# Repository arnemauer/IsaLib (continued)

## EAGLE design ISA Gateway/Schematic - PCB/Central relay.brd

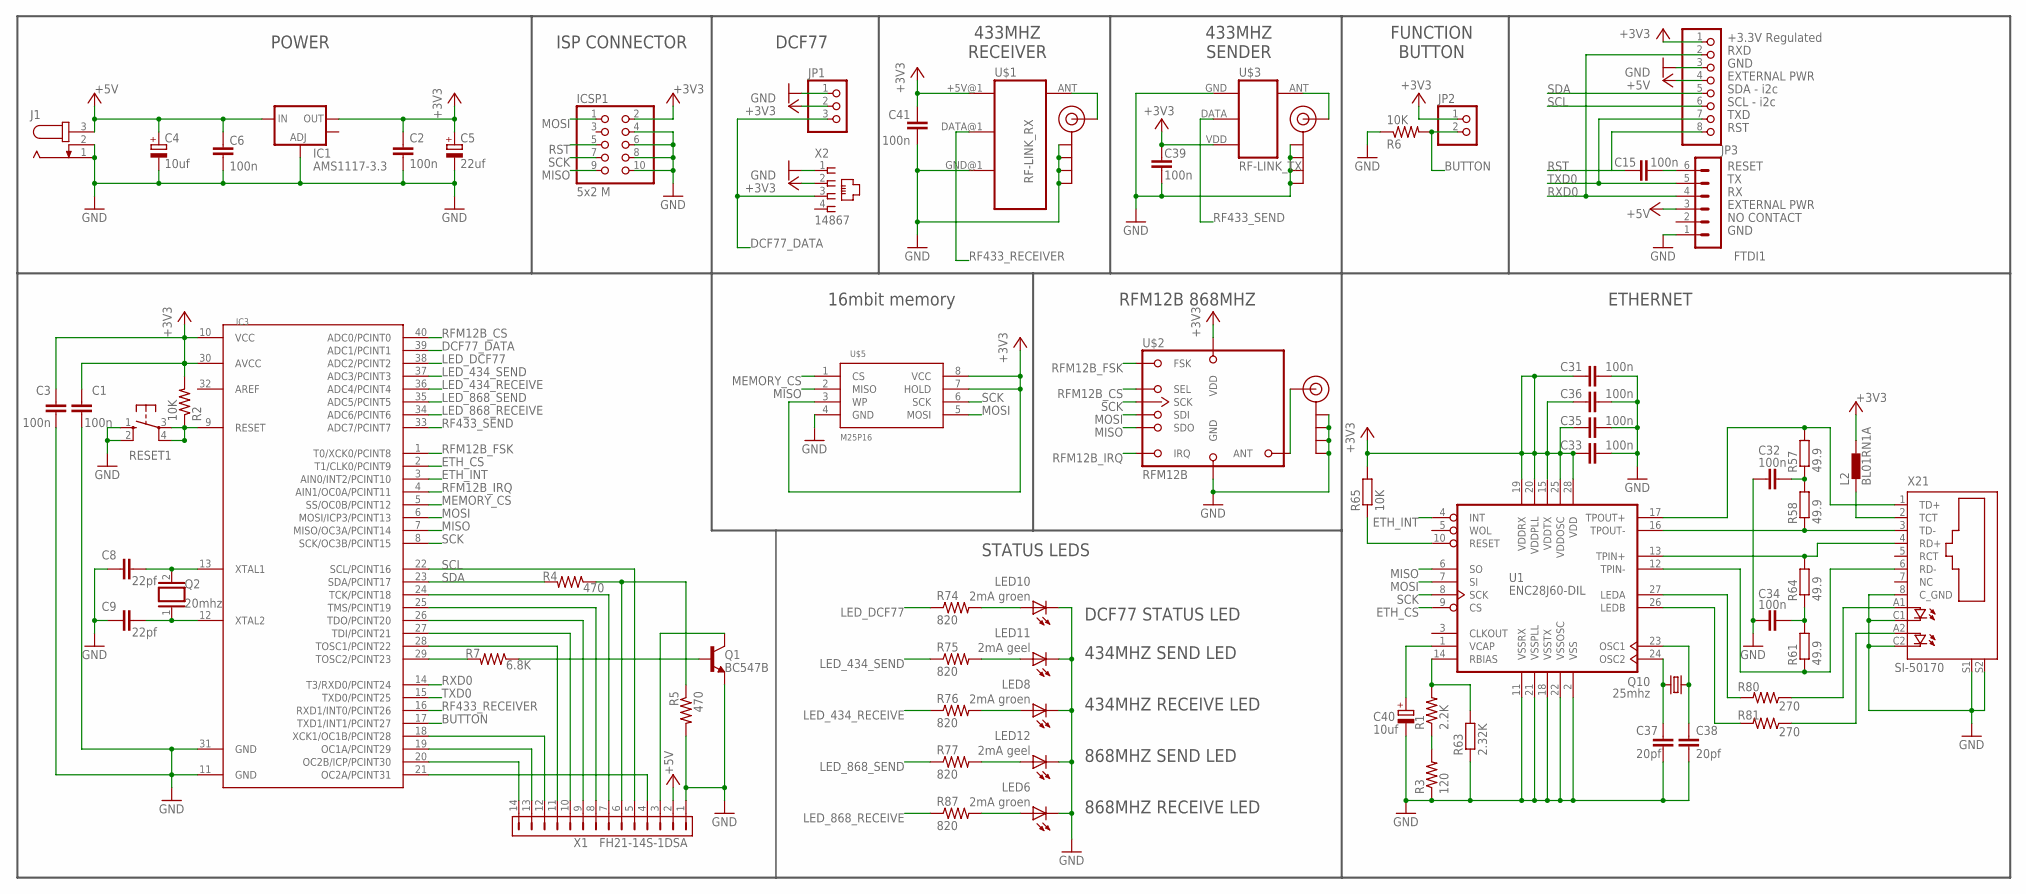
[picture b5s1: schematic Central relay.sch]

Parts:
C1, C2, C3, C6, C31, C32, C33, C34, C35, C36, C39, C41: 100n; 0805
C4, C40: 10uf; E2,5-6E
C5: 22uf; E2,5-6E
C8, C9: 22pf; 0805
C15: 100n; C025-025X050
C37, C38: 20pf; 0805
FTDI1: FTDI; MA06-1
IC1: AMS1117-3.3; SOT223
IC3: MEGA1284P; DIL40
ICSP1: 5x2 M; 2X05
J1: JACK-PLUG0; SPC4077
J$1, J$2, J$3: SMA_EDGE; SMA-EDGE
JP1: PINHD-1X3; 1X03
JP2: PINHD-1X2; 1X02
JP3: PINHD-1X8; 1X08
L2: BL01RN1A
LED6, LED8, LED10: 2mA groen; LED5MM
LED11, LED12: 2mA geel; LED5MM
Q1: BC547B; TO92
Q2: 20mhz; QS
Q10: 25mhz; HC49/S
R1: 2.2K; 0805
R2, R6: 10K; 0805
R3: 120; 0805
R4, R5: 470; 0805
R7: 6.8K; 0805
R57, R58, R61, R64: 49.9; 0207/7
R63: 2.32K; 0207/7
R65: 10K; 0207/7
R74, R75, R76, R77, R87: 820; 0805
R80, R81: 270; 0805
RESET1: 10-XX; B3F-10XX
U1: ENC28J60-DIL; DIL28-3
U$1: RF-LINK_RX
U$2: RFM12B; RFM12B-BREAKOUT-BASE
U$3: RF-LINK_TX
U$5: M25P16; SO08
X1: FH21-14S-1DSA
X2: 14867
X21: SI-50170

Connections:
+3V3: C1.2, C2.2, C3.2, C5.+, C31.1, C33.1, C35.2, C36.2, C39.2, C41.1, IC1.2 (OUT), IC3.10 (VCC), IC3.30 (AVCC), ICSP1.2, JP1.2, JP2.1, JP3.1, L2.2, R2.2, R65.2, U1.15 (VDDTX), U1.19 (VDDRX), U1.20 (VDDPLL), U1.25 (VDDOSC), U1.28 (VDD), U$1.+5V@1 (+5V), U$2.9 (VDD), U$3.VDD (GND), U$5.3 (WP), U$5.7 (HOLD), U$5.8 (VCC), X2.2
+5V: C4.+, C6.2, FTDI1.3, IC1.3 (IN), J1.3, JP3.4, X1.2
BUTTON: IC3.17 (TXD1/INT1/PCINT27), JP2.2, R6.2
DCF77_DATA: IC3.39 (ADC1/PCINT1), JP1.3, X2.3
ETH_CS: IC3.2 (T1/CLK0/PCINT9), U1.9 (CS)
ETH_INT: IC3.3 (AIN0/INT2/PCINT10), U1.4 (INT)
GND: C1.1, C2.1, C3.1, C4.-, C5.-, C6.1, C8.2, C9.2, C31.2, C32.1, C33.2, C34.1, C35.1, C36.1, C37.1, C38.1, C39.1, C40.-, C41.2, FTDI1.1, IC1.1 (ADJ), IC3.11 (GND), IC3.31 (GND), ICSP1.4, ICSP1.6, ICSP1.8, ICSP1.10, J1.1, J1.2, J$1.GND@0 (GND), J$1.GND@1 (GND), J$1.GND@2 (GND), J$1.GND@3 (GND), J$2.GND@0 (GND), J$2.GND@1 (GND), J$2.GND@2 (GND), J$2.GND@3 (GND), J$3.GND@0 (GND), J$3.GND@1 (GND), J$3.GND@2 (GND), J$3.GND@3 (GND), JP1.1, JP3.3, LED6.K (C), LED8.K (C), LED10.K (C), LED11.K (C), LED12.K (C), Q1.1 (E), R3.1, R5.2, R6.1, R63.1, RESET1.1 (S), RESET1.2 (S1), U1.2 (VSS), U1.11 (VSSRX), U1.18 (VSSTX), U1.21 (VSSPLL), U1.22 (VSSOSC), U$1.GND@1 (GND), U$2.10 (GND), U$3.GND (+5V), U$5.4 (GND), X1.1, X2.1, X21.8 (C_GND), X21.C1 (C), X21.C2 (C1), X21.S1, X21.S2
LED_434_RECEIVE: IC3.36 (ADC4/PCINT4), R76.1
LED_434_SEND: IC3.37 (ADC3/PCINT3), R75.1
LED_868_RECEIVE: IC3.34 (ADC6/PCINT6), R87.1
LED_868_SEND: IC3.35 (ADC5/PCINT5), R77.1
LED_DCF77: IC3.38 (ADC2/PCINT2), R74.1
MEMORY_CS: IC3.5 (SS/OC0B/PCINT12), U$5.1 (CS)
MISO: IC3.7 (MISO/OC3A/PCINT14), ICSP1.9, U1.6 (SO), U$2.1 (SDO), U$5.2 (MISO)
MOSI: IC3.6 (MOSI/ICP3/PCINT13), ICSP1.1, U1.7 (SI), U$2.12 (SDI), U$5.5 (MOSI)
unnamed: J$2.SIG (SIGNAL), U$1.ANT
unnamed: R80.1, X21.A1 (A)
unnamed: J$3.SIG (SIGNAL), U$3.ANT
unnamed: R1.1, R3.2
unnamed: R1.2, R63.2, U1.14 (RBIAS)
unnamed: R81.1, X21.A2 (A1)
unnamed: LED8.A, R76.2
unnamed: IC3.21 (OC2A/PCINT31), X1.4
unnamed: Q1.3 (C), X1.3
unnamed: Q1.2 (B), R7.1
unnamed: R4.1, R5.1, X1.6
unnamed: IC3.29 (TOSC2/PCINT23), R7.2
unnamed: LED11.A, R75.2
unnamed: IC3.24 (TCK/PCINT18), X1.7
unnamed: IC3.25 (TMS/PCINT19), X1.8
unnamed: IC3.26 (TDO/PCINT20), X1.9
unnamed: LED10.A, R74.2
unnamed: IC3.27 (TDI/PCINT21), X1.10
unnamed: IC3.28 (TOSC1/PCINT22), X1.11
unnamed: LED6.A, R87.2
unnamed: LED12.A, R77.2
unnamed: C8.1, IC3.13 (XTAL1), Q2.2
unnamed: L2.1, X21.2 (TCT)
unnamed: C34.2, R61.2, R64.1
unnamed: R57.2, U1.17 (TPOUT+), X21.1 (TD+)
unnamed: R58.1, U1.16 (TPOUT-), X21.3 (TD-)
unnamed: IC3.20 (OC2B/ICP/PCINT30), X1.14
unnamed: IC3.19 (OC1A/PCINT29), X1.13
unnamed: IC3.18 (XCK1/OC1B/PCINT28), X1.12
unnamed: C9.1, IC3.12 (XTAL2), Q2.1
unnamed: C15.2, FTDI1.6
unnamed: R64.2, U1.13 (TPIN+), X21.4 (RD+)
unnamed: R61.1, U1.12 (TPIN-), X21.6 (RD-)
unnamed: C37.2, Q10.1, U1.24 (OSC2)
unnamed: C38.2, Q10.2, U1.23 (OSC1)
unnamed: C40.+, U1.1 (VCAP)
unnamed: R65.1, U1.10 (RESET)
unnamed: C32.2, R57.1, R58.2
unnamed: R80.2, U1.27 (LEDA)
unnamed: R81.2, U1.26 (LEDB)
unnamed: J$1.SIG (SIGNAL), U$2.8 (ANT)
RF433_RECEIVER: IC3.16 (RXD1/INT0/PCINT26), U$1.DATA@1 (DATA)
RF433_SEND: IC3.33 (ADC7/PCINT7), U$3.DATA
RFM12B_CS: IC3.40 (ADC0/PCINT0), U$2.14 (SEL)
RFM12B_FSK: IC3.1 (T0/XCK0/PCINT8), U$2.3 (FSK)
RFM12B_IRQ: IC3.4 (AIN1/OC0A/PCINT11), U$2.2 (IRQ)
RST: C15.1, IC3.9 (RESET), ICSP1.5, JP3.8, R2.1, RESET1.3, RESET1.4 (P1)
RXD0: FTDI1.4, IC3.14 (T3/RXD0/PCINT24), JP3.2
SCK: IC3.8 (SCK/OC3B/PCINT15), ICSP1.7, U1.8 (SCK), U$2.13 (SCK), U$5.6 (SCK)
SCL: IC3.22 (SCL/PCINT16), JP3.6, X1.5
SDA: IC3.23 (SDA/PCINT17), JP3.5, R4.2
TXD0: FTDI1.5, IC3.15 (TXD0/PCINT25), JP3.7

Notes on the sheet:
GND
EXTERNAL PWR
NO CONTACT
RESET
SCL - i2c
SDA - i2c
433MHZ SENDER
433MHZ RECEIVER
ISP CONNECTOR
ETHERNET
RFM12B 868MHZ
STATUS LEDS
868MHZ RECEIVE LED
868MHZ SEND LED
434MHZ SEND LED
434MHZ RECEIVE LED
16mbit memory
DCF77
DCF77 STATUS LED
POWER
+3.3V Regulated
RXD
TXD
RST
FUNCTION BUTTON

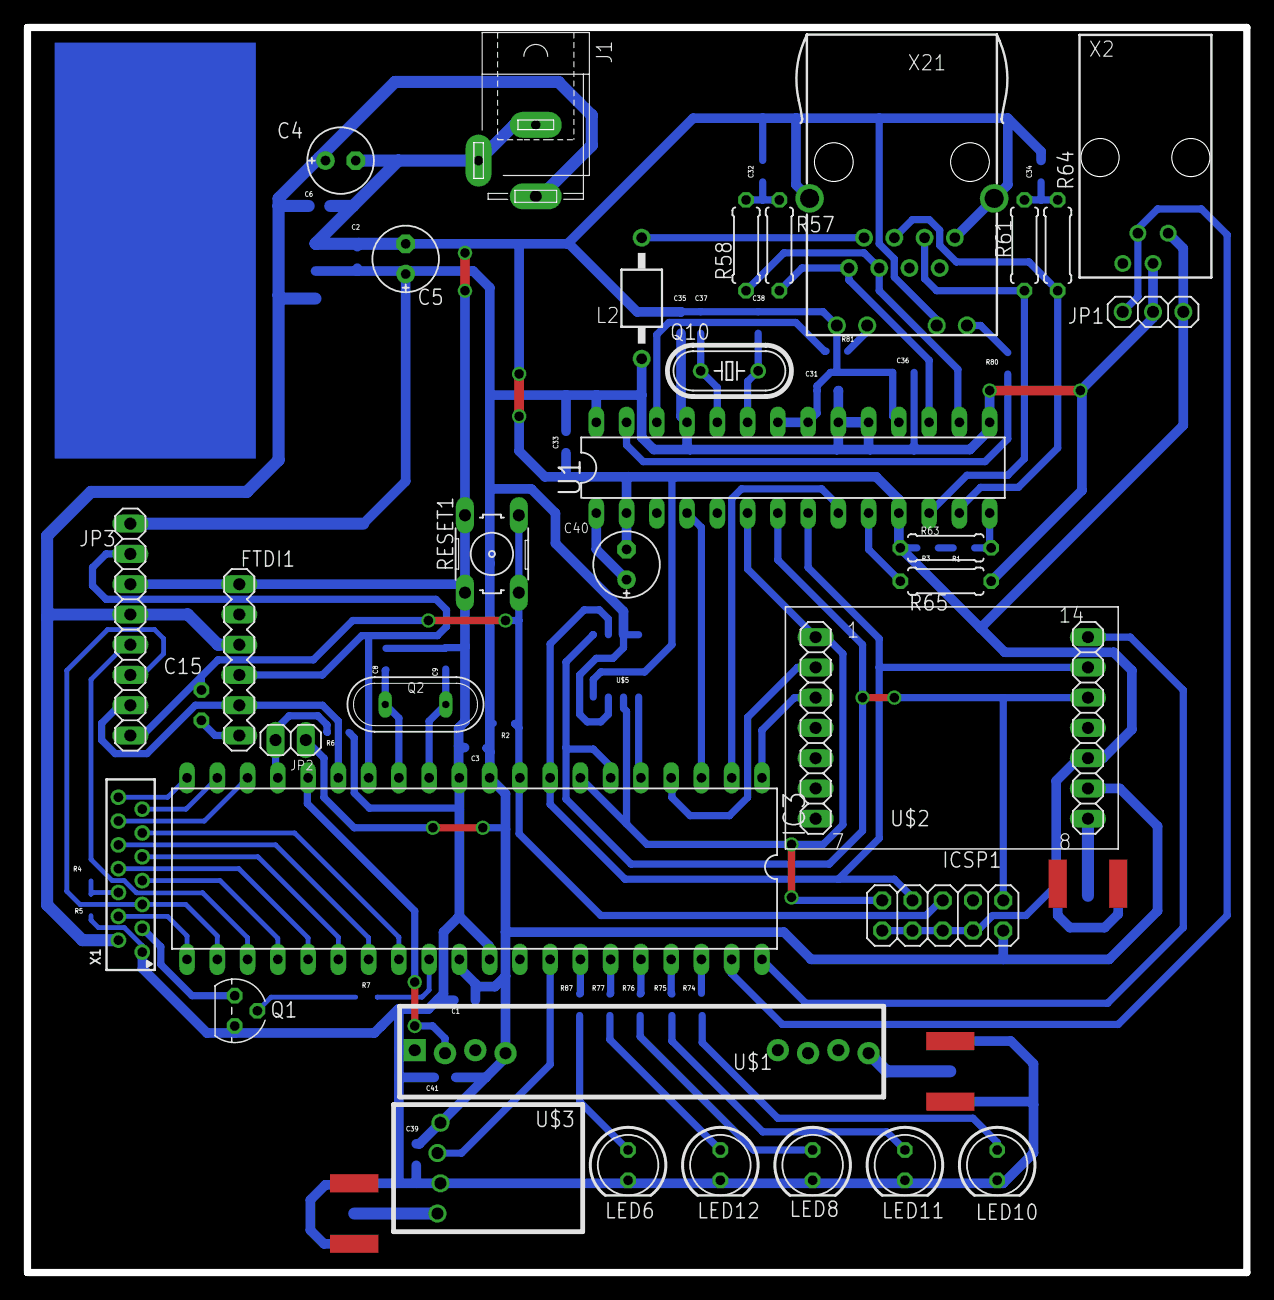
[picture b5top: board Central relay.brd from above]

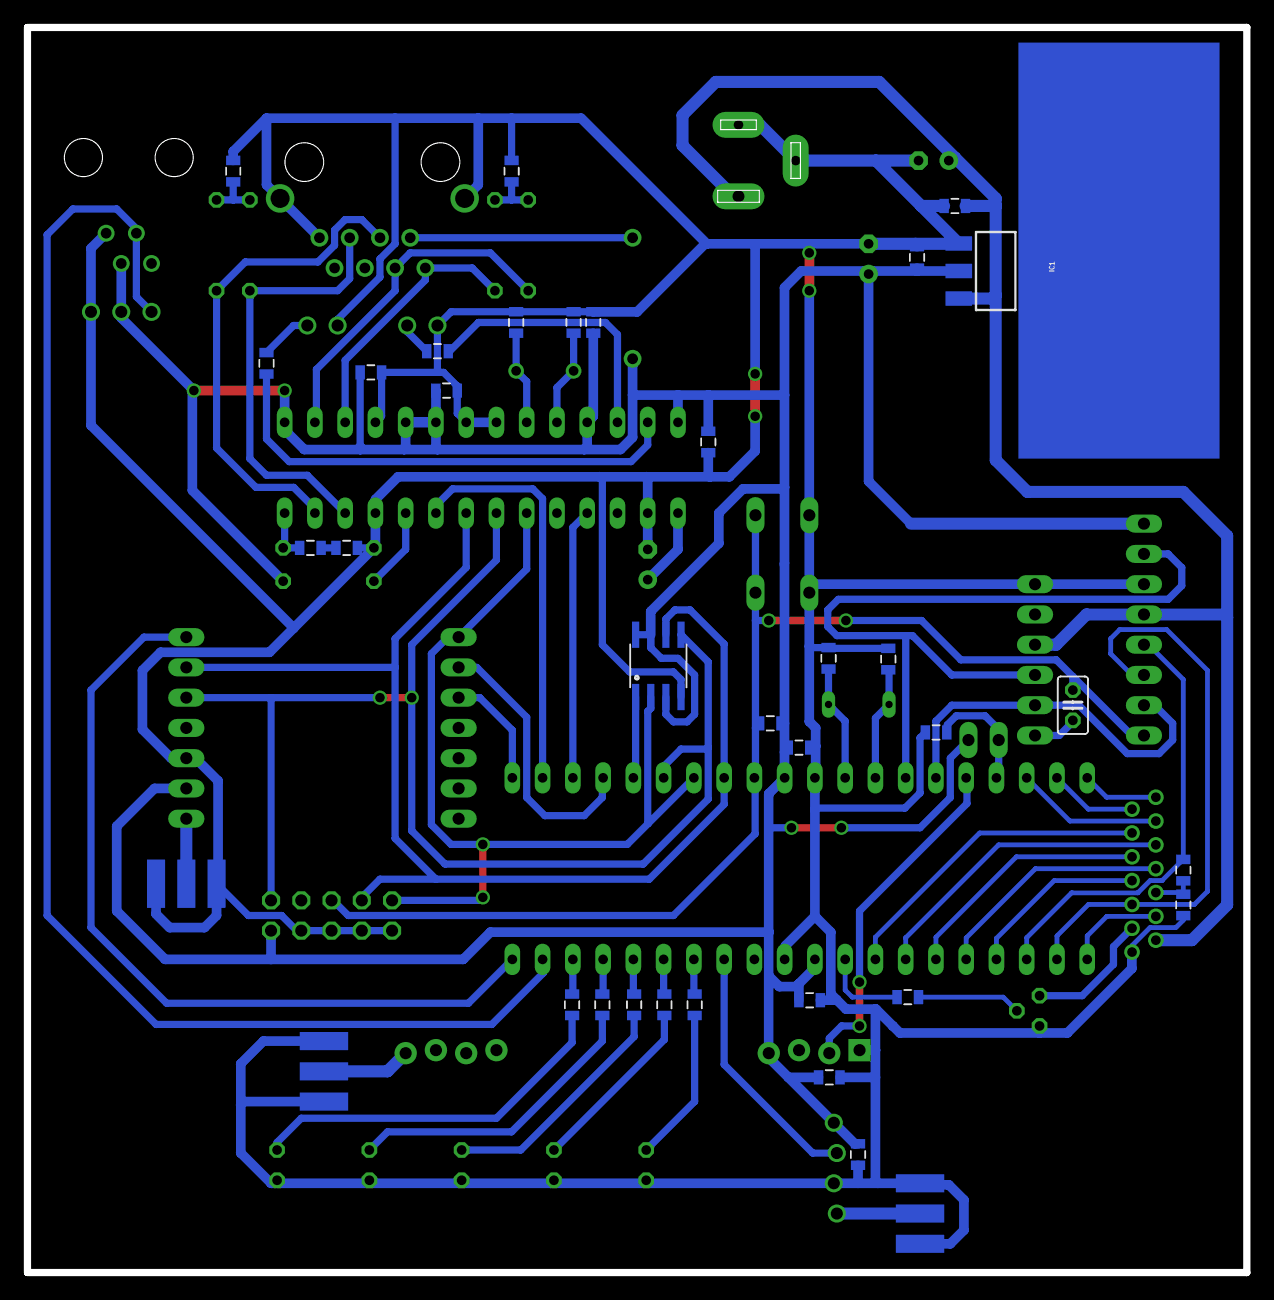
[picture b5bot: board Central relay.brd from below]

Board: 2 copper layers, 102.4 x 104.5 mm, 69 parts (36 on the bottom side), 67 nets.

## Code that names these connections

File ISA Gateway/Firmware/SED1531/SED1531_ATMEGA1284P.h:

#ifndef SED1531_ATMEGA1284P_H
#define SED1531_ATMEGA1284P_H

/*
    This file defines the pin mapping between the GLCD and the Arduino

    This file is part of the SED1531 Arduino library.

    SED1531 Arduino library Copyright (c) 2013 Tom van Zutphen
    http://www.tkkrlab.nl/wiki/Glcd_48x100

    This library is largely based on / ported from from the
    library (c) 2013 by Peter van Merkerk
    http://sourceforge.net/p/glcdsed1531lib/wiki/Home/

    I adapted it for use with Arduino and added some commands to draw circles,
    make it compatible with the arduino print command and add collision detect
    for all drawing functions except text.

    The SED1531 Arduino library is free software: you can redistribute it and/or
    modify it under the terms of the GNU General Public License as published
    by the Free Software Foundation, either version 3 of the License, or (at
    your option) any later version.

    The SED1531 Arduino library is distributed in the hope that it will be useful,
    but WITHOUT ANY WARRANTY; without even the implied warranty of
    MERCHANTABILITY or FITNESS FOR A PARTICULAR PURPOSE. See the GNU General
    Public License for more details.

    You should have received a copy of the GNU General Public License along with
    the SED1531 Arduino library If not, see http://www.gnu.org/licenses/.
*/

/*
    by default this library uses a different pin mapping for the data pins then the other code examples!

    Port and pin mapping for ATMEGA1284P @ 16MHz:

    AVR      	GLCD
    -----    	----
    PD6 (20)   	A0 (4)
    PC7 (29)   	RW (5)
    PC0 (22)    E  (6)
	
	PC6 (28)	D7 (7)
	PD5 (19)	D6 (8)
	PC5	(27)	D5 (9)
	PC1	(23)	D4 (10)
	PC4	(26)	D3 (11)
	PD4	(18)	D2 (12)
	PC3	(25)	D1 (13)
	PC2	(24)	D0 (14)
		

*/


#define GLCD_IO_INIT()	DDRC |= (1 << 0) | (1 << 7); DDRD |= (1 << 6) // PD6 (AO) is output


#define GLCD_IO_PIN_A0_0()              PORTD &= ~(1 << 6)
#define GLCD_IO_PIN_A0_1()              PORTD |= (1 << 6)

#define GLCD_IO_PIN_RW_0()              PORTC &= ~( 1 << 7)
#define GLCD_IO_PIN_RW_1()              PORTC |= (1 << 7)

#define GLCD_IO_PIN_E_0()               PORTC &= ~(1 << 0)
#define GLCD_IO_PIN_E_1()               PORTC |= (1 << 0)

#define GLCD_IO_DATA_DIR_INPUT() DDRC &= ~((1 << 1) | (1 << 2) | (1 << 3) | (1 << 4) | (1 << 5) | (1 << 6)); DDRD &= ~((1 << 4) | (1 << 5))
// pins input

// pins input
#define GLCD_IO_DATA_DIR_OUTPUT()	DDRC |= (1 << 1) | (1 << 2) | (1 << 3) | (1 << 4) | (1 << 5) | (1 << 6); DDRD |= (1 << 4) | (1 << 5)


/*
 * Option 1:
 * GLCD D0..D1 = Arduino PIN8..PIN9 (Atmega328 PB0..PB1)
 * GLCD D2..D7 = Arduino PIN2..7 (Atmega328 PD2..PD7)
 */
					//cli(); WHY?! 
//(PC2>D0 en PC3>D1), (PC4>D3), (PC1>D4), (PC5>D5), PC6>D7)     
// (PD4>D2), (PD5>D6)                               
#define GLCD_IO_DATA_OUTPUT(data)		uint8_t register saveSreg = SREG; PORTC = (PORTB & 0B01111110) | ((data&0B11)<<2) | ((data&0B1000) <<1) | ((data&0B10000)>>3) | (data&0B100000) | ((data&0b10000000)>>1) ; PORTD = (PORTD & 0B11001111) | ((data&0B01000000)>> 1) | ((data&0B00000100)<< 2); SREG=saveSreg
												// D1 D0				// D2					// D3					// D4			// D5				// D6					// D7
#define GLCD_IO_DATA_INPUT()           (((PINC &0B1100)>>2) | ((PIND &0B10000)>>2) | ((PINC &0B10000)>>2) | ((PINC &0B10)<<3) | (PINC &0B100000) | ((PIND &0b100000)<<1) | ((PINC &0B1000000)<<1))


/*
 * Option 2:
 * GLCD D6..D7 = Arduino PIN8..PIN9 (ATmega328 PB0..PB1)
 * GLCD D0..D5 = Arduino PIN2..7 (ATmega328 PD2..PD7)
 */
//#define GLCD_IO_DATA_OUTPUT(data)		uint8_t register saveSreg = SREG; \
										cli();                                      \
										PORTB = (PORTB & 0B11111100) | (data>>6); \
										PORTD = (PORTD & 0B11) | (data<<2); \
										SREG=saveSreg
//#define GLCD_IO_DATA_INPUT()           (((PIND & 0B11111100)>>2) | ((PINB & 0B11)<<6))


#define GLCD_IO_DELAY_READ()           __asm volatile ("nop\nnop\nnop")					//each nop = 62,5ns @16mhz
//#define GLCD_IO_DELAY_WRITE()

#endif // #ifndef SED1531_ATMEGA1284P_H

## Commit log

2013-10-27 RFM12B library + 2 projects (isa gateway + ISA doorbell)
2013-10-28 Pictogrammen voor in de lamp toegevoegd
2013-10-28 Foto's van lamp met pictogrammen toegevoegd
2013-10-29 Schema ISA ouderen lamp toegevoegd
2013-10-29 Eerste schema met led printplaten
2013-10-30 Weerstanden toegevoegd aan led printplaten, connecties led prints gemaakt
2013-10-31 Led pcb gemaakt
2013-11-01 Board + schema
    http://dickbest.nl/index.php?_a=viewProd&productId=11468
2013-11-03 Aanpassing pcb en schema
2013-11-04 Aanpassing PCB
2013-11-15 TLC5490 toegevoegd om pwm functies te behouden, timer 0 en 1 nodig voor geluid!, schema aangepast.
2013-11-16 TLC5490 vervangen door PCA9635 ivm standby stroomverbruik en componenten
2013-11-16 PCA9635 toegevoegd, atmega omgezet naar SMD. Schema klaar. nu board nog.
2013-11-17 PCB aangepast
2013-11-18 PCB afgemaakt
2013-11-20 BOM toegevoegd
2013-11-20 weerstanden voor de rgb leds toegevoegd
2013-11-23 Arduino TONE AC toegevoegd, volgende keer -> omzetten naar C + toevoegen verschillende geluiden!!
2013-11-23 Piezo code in orde gemaakt. Deurbel, telefoon, whoop alarm toegevoegd.
2013-11-24 SOS geluid toegevoegd, fout in Deurbelgeluid verbeterd (delay toegevoegd).
2013-11-26 methodes om piezo aan te sturen
2013-11-27 Spoel toegevoegd voor opzwepen piezo
2013-11-29 pull-up weerstanden op sda / dcl lijn toegevoegd
2013-11-29 PCB afgemaakt, BOM lijst aangevuld.
2013-11-30 BOM uitgebreid met prijzen
2013-12-01 Bestanden met metingen deurbel toegevoegd
2013-12-01 BOM lijst aangepast, waarde van weerstanden RGB LEDS berekent, juiste transistor voor piezo element.
2013-12-07 Een print met daarop 5mm rgb leds ipv 4 losse printjes met smd leds. Dit ivm de ruimte in de lamp voor de batterijen. Kostprijs is ook lager :P
2013-12-09 Reset push button toegevoegd + voor een deel PCB aangepast aan nieuwe RGB 5mm leds.
2013-12-10 TODO: weerstanden bij leds vervangen zodat voeding eronder kan lopen. Weerstanden bij reset en SDA SCL vervangen door normale
2013-12-11 PCB aanpassingen
2013-12-11 Spoorbreedtes aangepast voor de PCA9635. Weerstanden voor witte leds toegevoegd. PCB afgemaakt.
2013-12-11 Kleine aanpassingen aan PCB
2013-12-13 groundplane toegevoegd
2013-12-19 PIEZO speaker op poort timer 1 gezet ivm kleinere code, beter geluid, minder clock cycles.
2013-12-22 PIEZO op verkeerde pin gezet, pin veranderd en pcb aangepast.
2013-12-22 Code aanpassing
2013-12-22 Code aangepast -> kleine functie opbouw gemaak; c code voor aansturing pca9635 gevonden;
    uitzoeken: manier van aansturen leds dmv patterns. bijv. in arrays? of...
2013-12-23 Begin Flowchart voor programma gemaakt
2013-12-26 i2c master lib toegevoegd; begin pca9635 library gemaakt, werkt :)
2013-12-29 code opgeschoond, testcode voor rfm12b erin gezet. 99% packet loss, waarschijnlijk module kapot. Nieuwe module besteld.
2014-01-02 kleine code wijzigingen, na int geen uitvoering van while loop.. ?
2014-01-02 slaap nog niet werkend, interrupt zorgt er niet voor dat loop weer begin te lopen...
2014-01-03 Sleep ok door verwijderen van uart debug info.
2014-01-03 verwerking pakket naar actieve alarm array werkend.
2014-01-04 proberen om struct array in progmem te persen.
2014-01-07 struct in progmem retourneert verschillende waardes over uart0
2014-01-08 Probleem array in progmem opgelost!
2014-01-09 while loop klaar; TODO: ISR timer 2, led patronen, geluidspatronen
2014-01-09 Begin overname flowchart in C; aanpassingen in PCA9635; TODO: ISR timer 2
2014-01-11 aanpassingen
2014-01-11 Aanpassingen sound
2014-01-12 Kleine aanpasingen
2014-01-12 geluidsduur in interrupt klopt niet, duur is te kort en lijkt niet uit array te komen.
2014-01-12 Geluid, flash, en icoon werkt. TODO: bug in geluid!
2014-01-13 Code aangepast; Alles werkt!
2014-01-17 sleep aanpassingen
2014-02-01 Aanpassing gemaakt om uc in diepe slaap te krijgen. TODO: low duty cycle instellen voor de RFM12B http://harizanov.com/2012/11/low-power-receiver-options/
2014-02-02 Kristal vervangen door keramisch type. Na versturen van pakket licht led 1 maal op, daarna geen andere interrupts. Uitzoeken ivm power dwn.
2014-02-03 Fuse veranderd naar 0x05 ivm error. 0x05 == 0xFD.
2014-02-06 no message
2014-04-02 final -> sleep send other commands than standby??
2014-04-09 Schema voor zender gemaakt. Telefoondeel toegevoegd. TODO: deurbel deel.
2014-04-10 weerstand berkeent voor 6n138
2014-04-11 Kleine verandering in schema zender
2014-04-18 6n138 toegevoegd voor telefoondetectie en deurbeldetectie + weerstand berekening.
2014-04-20 board aanpassingne
2014-04-24 testcode gemaakt
2014-04-30 testcode wijzigingen
2014-05-01 Test waarom standby stand wel de data goed verwerkt en bij power-down niet. Bij standby is er weinig tijd tussen de interrupt van de rfm12b en het vervolgens uitlezen van de bytes uit de rfm12b. Bij 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
2014-05-06 Code klaar en werkend
2014-05-07 Code cleanup
2014-05-14 Kleine aanpassingen
2014-05-14 Kleine wijzigingen en foutopsporing
2014-05-16 Kleine wijzigingen om fouten op te sporen.
2014-05-16 Zuiniger gemaakt. Na ontvangst van aantal testbytes reageert de lamp niet meer. Schakelt opnieuw naar idle en daarna niets?!
2014-05-19 Kleine aanpassingen. Alles werkt naar behoren. ACK terugsturen voor broadcast message erin gezet.
2014-05-20 Compleet werkend!
    Kleine aanpassingen in de code:
    - CRC check NA rf12_recvdone(); bij een pakket met verkeerde CRC gaat de uc slapen en zal de rfm12b radio niet meer uit idle halen. De while loop moet dan nog een keer starten ipv direct slapen.
    - aanpassingen geluid van hulp
    - aanpassingen in icon licht; stap 11 (100% aan) korter gemaakt.
2014-05-21 Voorbereidingen getroffen voor Deurbelzender en een losse telefoonzender.
2014-05-24 Zender deurbel schema en pcb aangepast
2014-05-24 Kleine aanpasingen pcb zender
2014-05-28 kleine pcb wijzigingen
2014-05-29 pcb bijna klaar
2014-05-31 kleine wijzigingen in pcb
2014-05-31 Wijzingen in PCB, bijna klaar!
2014-06-02 PCB ready!
2014-06-02 Kleine fouten in pcb aangepast: - batterijhouder naar de achterkant - wirepad verder uit elkaar
2014-06-08 Wijziging BOM en kleine wijziging onderdelen in schema.
2014-07-06 Wijzigingen in zender firmware ivm rfm69w. Voorbereiding zender gemaakt. Libs oké. Todo: mainloop met int check en daarna sleep.
2014-07-26 Allerhande aanpassingen
2014-08-01 temp
2014-09-13 RFM12B vervangen door RFM69 + transistor toegevoegd voor interrupt
2014-09-16 lamp ontvanger interrupt tijdens zenden aangepast. Interrupt na verzending pakket blijft totdat de modes aangepast is. Omdat interrupt low bleef doorgaan kreeg cpu geen mogelijkheid om modes te veran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
2014-09-20 Alles werkend -> probleem was losse antenne... TODO->activeren listen mode
